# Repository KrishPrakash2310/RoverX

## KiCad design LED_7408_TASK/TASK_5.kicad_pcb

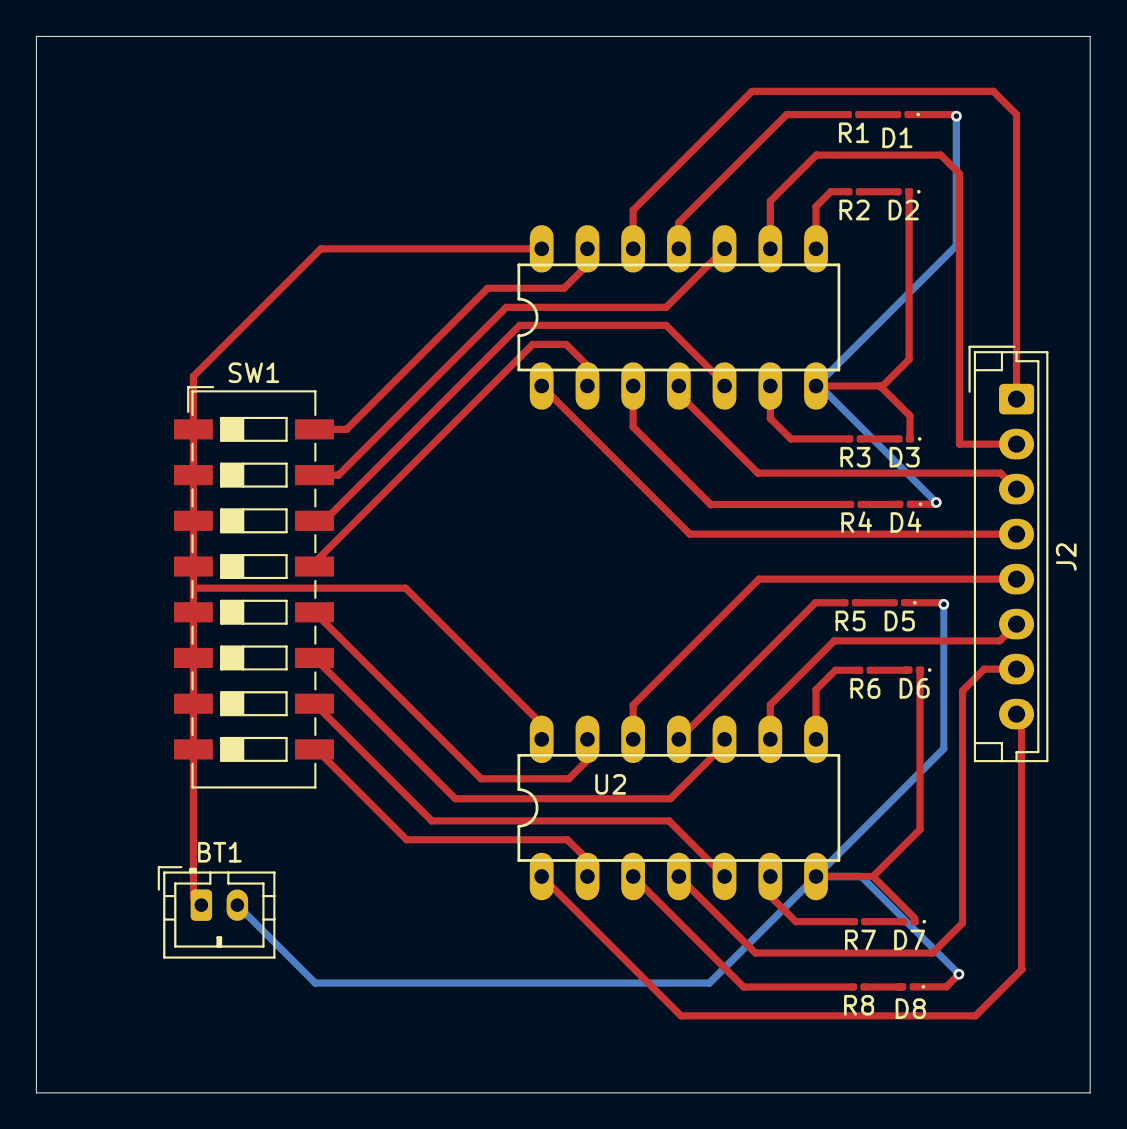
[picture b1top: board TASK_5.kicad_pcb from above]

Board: 2 copper layers, 58.5 x 58.7 mm, 21 parts (0 on the bottom side), 34 nets.

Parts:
BT1: Battery; JST_PH_B2B-PH-K_1x02_P2.00mm_Vertical
D1, D2, D3, D4, D5, D6, D7, D8: LED; LED_0201_0603Metric
J2: Conn_01x08_Pin; JST_EH_B8B-EH-A_1x08_P2.50mm_Vertical
R1, R2, R3, R4, R5, R6, R7, R8: R; R_0201_0603Metric
SW1: SW_DIP_x08; SW_DIP_SPSTx08_Slide_6.7x21.88mm_W6.73mm_P2.54mm_LowProfile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
U1, U2: DIL14

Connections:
5V: BT1.1 (+), SW1.1, SW1.2, SW1.3, SW1.4, SW1.5, SW1.6, SW1.7, SW1.8, U1.14 (VCC), U2.14 (VCC)
/oc1: J2.1, U1.12 (IB4)
/oc2: J2.2, U1.9 (IB3)
/oc3: J2.3, U1.4 (IA2)
/oc4: J2.4, U1.1 (IA1)
/oc5: J2.5, U2.12 (IB4)
/oc6: J2.6, U2.9 (IB3)
/oc7: J2.7, U2.4 (IA2)
/oc8: J2.8, U2.1 (IA1)
/od1: SW1.16, U1.13 (IA4)
/od2: SW1.15, U1.10 (IA3)
/od3: SW1.14, U1.5 (IB2)
/od4: SW1.13, U1.2 (IB1)
/od5: SW1.12, U2.13 (IA4)
/od6: SW1.11, U2.10 (IA3)
/od7: SW1.10, U2.5 (IB2)
/od8: SW1.9, U2.2 (IB1)
GND: BT1.2 (-), D1.1 (K), D2.1 (K), D3.1 (K), D4.1 (K), D5.1 (K), D6.1 (K), D7.1 (K), D8.1 (K), U1.7 (GND), U2.7 (GND)
unnamed: D1.2 (A), R1.1
unnamed: D2.2 (A), R2.1
unnamed: D3.2 (A), R3.1
unnamed: D4.2 (A), R4.1
unnamed: D5.2 (A), R5.1
unnamed: D6.2 (A), R6.1
unnamed: D7.2 (A), R7.1
unnamed: D8.2 (A), R8.1
op1: R1.2, U1.11 (OG4)
op2: R2.2, U1.8 (OG3)
op3: R3.2, U1.6 (OG2)
op4: R4.2, U1.3 (OG1)
op5: R5.2, U2.11 (OG4)
op6: R6.2, U2.8 (OG3)
op7: R7.2, U2.6 (OG2)
op8: R8.2, U2.3 (OG1)

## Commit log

2024-06-26 Communication Protocols
2024-06-26 PCBs:Basic
2024-06-26 AttachInterrupt_TASK
2024-06-26 COMM. PROTOCOLS
2024-07-02 KiCAD First Task
2024-07-05 KiCAD TASK
2024-07-06 Breakout Board
